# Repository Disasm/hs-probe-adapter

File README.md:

# `hs-probe-adapter`

Adapter board for the [HS Probe](https://github.com/probe-rs/hs-probe) hardware probe.

Provides the following connectors:
* J2: 10-pin ARM SWD connector (1.27mm pitch)
* J3: UART connector (2.54mm pitch)
* J4: SWD connector (2.54mm pitch)
* J5: BluePill connector (2.54mm pitch)

J1 is the HS Probe connector (STDC14).

## Revision History

### 1.0: 2022-01-23

* First version.
* Errata:
    * J2 (ARM SWD) connector pinout is incorrect. Do not use it.

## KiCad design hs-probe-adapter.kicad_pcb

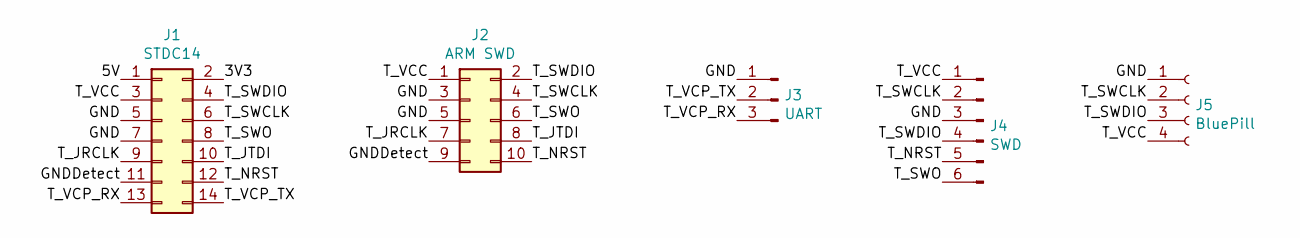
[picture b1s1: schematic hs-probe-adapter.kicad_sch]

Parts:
J1: STDC14; PinSocket_2x07_P1.27mm_Vertical_SMD
J2: ARM SWD; PinHeader_2x05_P1.27mm_Vertical_SMD
J3: UART; PinHeader_1x03_P2.54mm_Horizontal
J4: SWD; PinHeader_1x06_P2.54mm_Horizontal
J5: BluePill; PinSocket_1x04_P2.54mm_Horizontal

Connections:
/3V3: J1.2
/5V: J1.1
/GND: J1.5, J1.7, J2.3, J2.5, J3.1, J4.3, J5.1
/GNDDetect: J1.11, J2.9
/T_JRCLK: J1.9, J2.7
/T_JTDI: J1.10, J2.8
/T_NRST: J1.12, J2.10, J4.5
/T_SWCLK: J1.6, J2.4, J4.2, J5.2
/T_SWDIO: J1.4, J2.2, J4.4, J5.3
/T_SWO: J1.8, J2.6, J4.6
/T_VCC: J1.3, J2.1, J4.1, J5.4
/T_VCP_RX: J1.13, J3.3
/T_VCP_TX: J1.14, J3.2

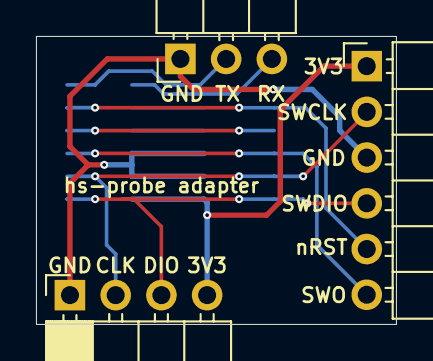
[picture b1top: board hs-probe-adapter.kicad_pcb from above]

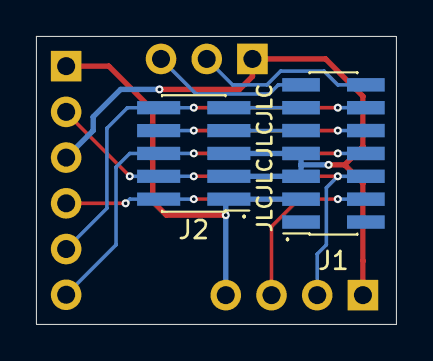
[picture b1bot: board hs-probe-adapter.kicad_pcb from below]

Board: 2 copper layers, 20.0 x 16.0 mm, 5 parts (2 on the bottom side), 11 nets.

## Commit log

2021-12-20 Add project files
2022-01-23 Convert to KiCad 6.0
2022-01-23 Add silkscreen
2022-01-23 Add gerbers
2023-12-31 Add readme
